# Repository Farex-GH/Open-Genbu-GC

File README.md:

# Open-Genbu-GC
Replacement PCB and firmware for Genbu Groove Coaster controllers

For firmware building and flashing instructions, see firmware/README.md.

Pre-built firmware is available in the Releases tab.

For PCB and schematic viewing, download KiCad and open the respective PCB/*.kicad_pro file.

## WIP

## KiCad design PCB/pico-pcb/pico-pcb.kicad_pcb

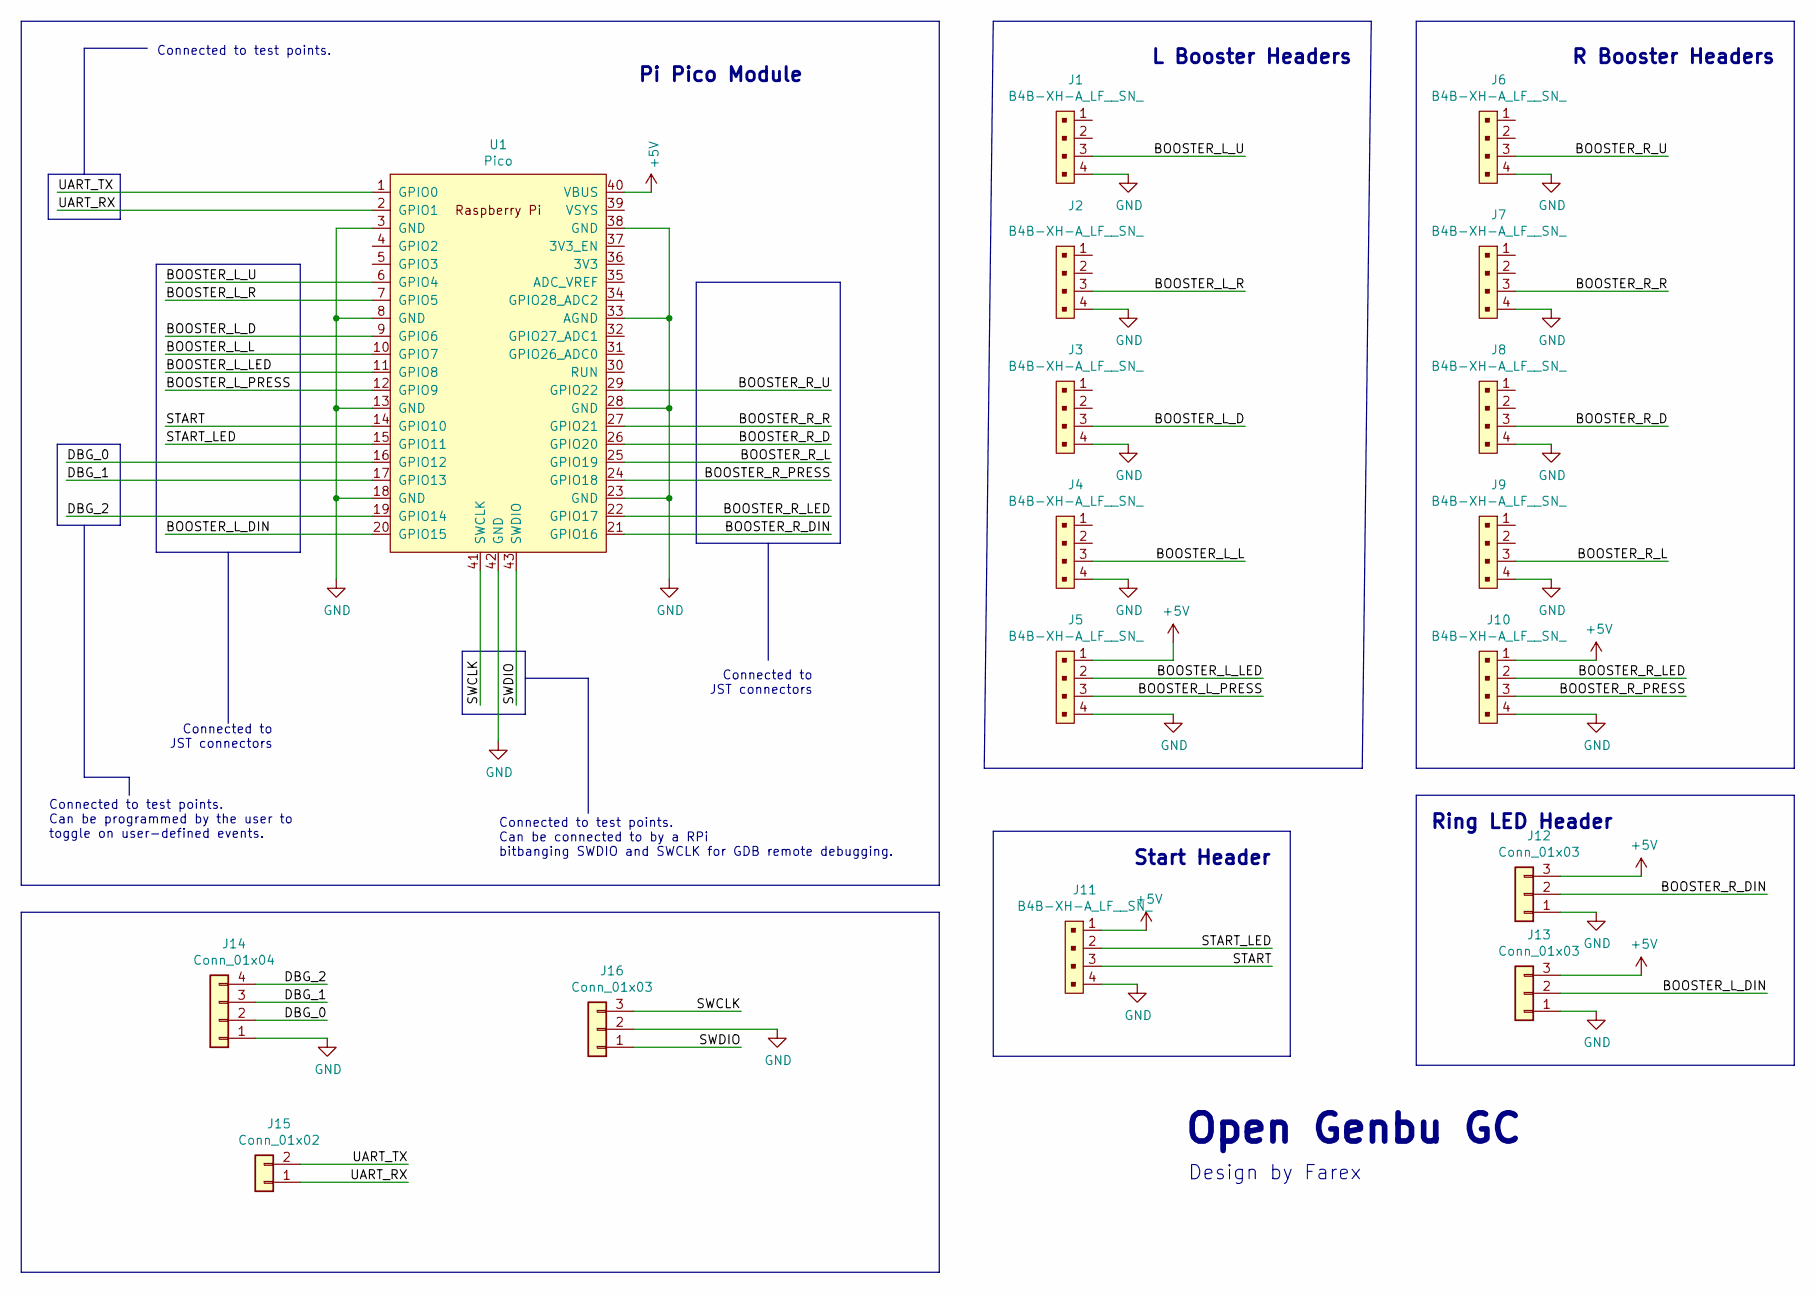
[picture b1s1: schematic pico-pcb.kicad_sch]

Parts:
J1, J2, J3, J4, J5, J6, J7, J8, J9, J10, J11: B4B-XH-A_LF__SN_; JST_B4B-XH-A(LF)(SN); MPN B4B-XH-A(LF)(SN); Digi-Key_PN 455-2249-ND
J12, J13, J16: Conn_01x03; PinSocket_1x03_P2.54mm_Vertical
J14: Conn_01x04; PinSocket_1x04_P2.54mm_Vertical
J15: Conn_01x02; PinSocket_1x02_P2.54mm_Vertical
U1: Pico; RPi_Pico_SMD_TH

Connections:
+5V: J5.1, J10.1, J11.1, J12.3, J13.3, U1.40 (VBUS)
/BOOSTER_L_D: J3.3, U1.9 (GPIO6)
/BOOSTER_L_DIN: J13.2, U1.20 (GPIO15)
/BOOSTER_L_L: J4.3, U1.10 (GPIO7)
/BOOSTER_L_LED: J5.2, U1.11 (GPIO8)
/BOOSTER_L_PRESS: J5.3, U1.12 (GPIO9)
/BOOSTER_L_R: J2.3, U1.7 (GPIO5)
/BOOSTER_L_U: J1.3, U1.6 (GPIO4)
/BOOSTER_R_D: J8.3, U1.26 (GPIO20)
/BOOSTER_R_DIN: J12.2, U1.21 (GPIO16)
/BOOSTER_R_L: J9.3, U1.25 (GPIO19)
/BOOSTER_R_LED: J10.2, U1.22 (GPIO17)
/BOOSTER_R_PRESS: J10.3, U1.24 (GPIO18)
/BOOSTER_R_R: J7.3, U1.27 (GPIO21)
/BOOSTER_R_U: J6.3, U1.29 (GPIO22)
/DBG_0: J14.2, U1.16 (GPIO12)
/DBG_1: J14.3, U1.17 (GPIO13)
/DBG_2: J14.4, U1.19 (GPIO14)
/START: J11.3, U1.14 (GPIO10)
/START_LED: J11.2, U1.15 (GPIO11)
/SWCLK: J16.3, U1.41 (SWCLK)
/SWDIO: J16.1, U1.43 (SWDIO)
/UART_RX: J15.1, U1.2 (GPIO1)
/UART_TX: J15.2, U1.1 (GPIO0)
GND: J1.4, J2.4, J3.4, J4.4, J5.4, J6.4, J7.4, J8.4, J9.4, J10.4, J11.4, J12.1, J13.1, J14.1, J16.2, U1.3 (GND), U1.8 (GND), U1.13 (GND), U1.18 (GND), U1.23 (GND), U1.28 (GND), U1.33 (AGND), U1.38 (GND), U1.42 (GND)

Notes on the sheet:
Connected to test points. Can be programmed by the user to toggle on user-defined events.
Connected to test points.
Connected to JST connectors
Pi Pico Module
R Booster Headers
Connected to test points. Can be connected to by a RPi bitbanging SWDIO and SWCLK for GDB remote debugging.
L Booster Headers
Ring LED Header
Start Header
Open Genbu GC
Design by Farex

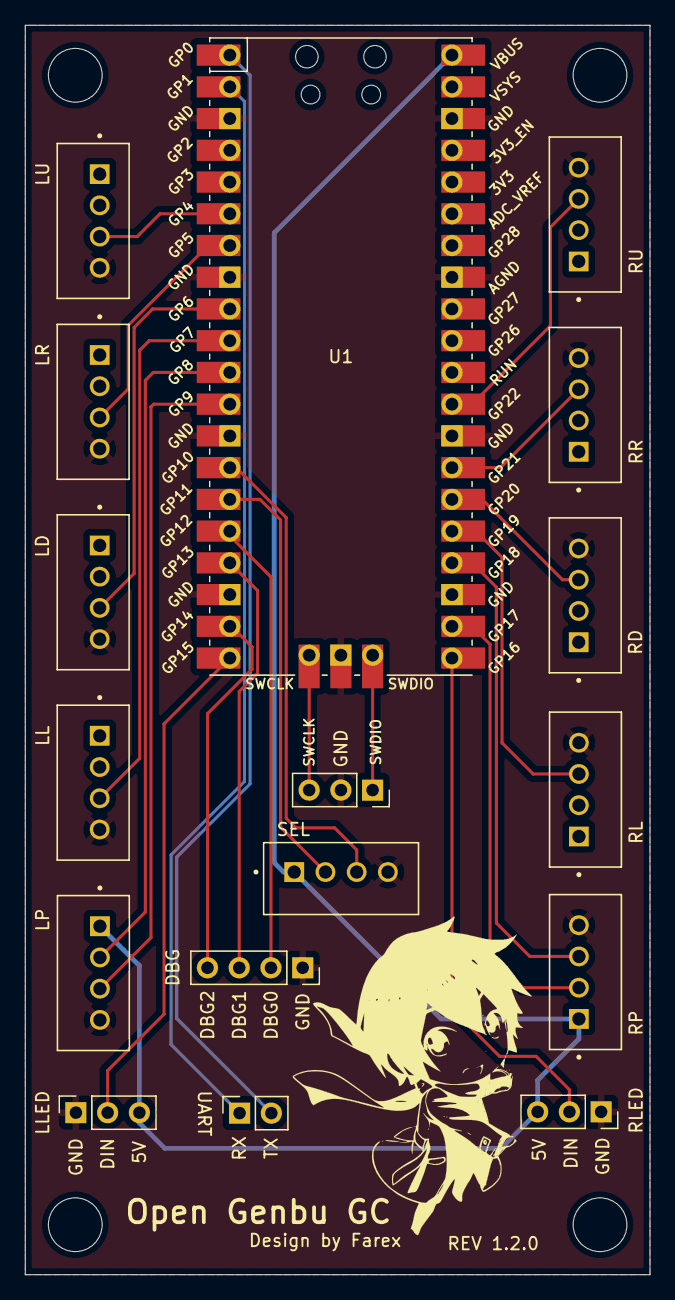
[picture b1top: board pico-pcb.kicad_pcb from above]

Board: 2 copper layers, 50.0 x 100.0 mm, 21 parts (0 on the bottom side), 25 nets.

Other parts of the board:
 : MountingHole_4.3mm_M4_ISO7380
 #2,  #3,  #4: MountingHole_4.3mm_M4_ISO7380

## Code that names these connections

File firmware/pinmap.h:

#ifndef PINMAP_H
#define PINMAP_H

#define BOOSTER_R_U 22
#define BOOSTER_R_R 21
#define BOOSTER_R_D 20
#define BOOSTER_R_L 19
#define BOOSTER_R_PRESS 18
#define BOOSTER_R_LED 17

#define BOOSTER_L_U 4
#define BOOSTER_L_R 5
#define BOOSTER_L_D 6
#define BOOSTER_L_L 7
#define BOOSTER_L_LED 8
#define BOOSTER_L_PRESS 9

#define BTN_START 10
#define BTN_START_LED 11

#define BOOSTER_L_WS2812_DIN 15
#define BOOSTER_L_NUM_WS2812 10
#define BOOSTER_R_WS2812_DIN 16
#define BOOSTER_R_NUM_WS2812 10

#define NUM_BTN 7
#define NUM_DPAD 4
#define NUM_WS2812 16

/*
 * Useful if we need to see where we are in code, but are in a time critical
 * situation where using a UART is too slow.
 */
#define PIN_DBG_0 12
#define PIN_DBG_1 13
#define PIN_DBG_2 14

#endif

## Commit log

2021-04-04 utils: pinmap: Add GPIO toggle code
2021-04-16 debug: Add GPIO debug code
    Eventually pin toggling within code will be removed later
2021-04-25 pinmap: Update GPIOs for PCB
2021-04-25 ws2812: Raise debug print threshold
    Lower threshold made it annoying to debug other problems, because CPU1
    would print in the middle of CPU0 printing.
2021-04-25 usb gamepad: Change button mapping ordering
    THe ordering is wrong because when developing, I had the buttons
    oriented the wrong way.
2021-04-25 debounce: board_io: Add debounce code
    v1 of debounce code, may be revised later.
    Button presses are very very very bouncy, so an ISR-driven pure firmware
    solution might not work.
2021-04-25 usb gamepad: Update mapping comments
2021-04-25 usb gamepad: Remove gamepad_held code
    Doesn't seem to be needed.
2021-04-25 board io: Misc comment fixes
2021-04-25 TODO: Update
2021-04-25 Debounce: Remove dead code
2021-04-25 proc_queue: Clarify single-core usage
2021-04-25 ws2812: Whitespace fixes
2021-04-25 main: Add LED feedback TODO
2021-04-25 usb driver: dead code and whitespace fixes
    No functional change
2021-04-25 usb driver: Add blurb saying how to use it
2021-04-25 descriptors: Change product name
2021-05-04 usb_driver: Pretty-fy setup packet handling
2021-05-04 descriptors: Use Genbu VID + PID
2022-03-07 firmware/TODO: Remove LED TODO
    LEDs were moved to the same core as USB execution.
2022-03-07 PCB/pico-pcb: Add rev 1.2.0
2022-03-07 README: Add some getting started info
2022-03-07 README.md: Point to built FW
2022-03-07 README.md.bak: Delete
2022-03-07 README.md: Fix formatting
2022-03-07 firmware/board_io: Remove dead code
